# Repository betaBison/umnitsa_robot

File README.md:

# umnitsa_robot
Umnitsa comes from the englsih transliteration of the russian word "умница" clever pesron or smarty-pants.
Umnitsa is designed to be a clever robot.  
  
See also [umnitsa_msgs](https://github.com/betaBison/umnitsa_msgs), [umnitsa_gs](https://github.com/betaBison/umnitsa_gs), amd [umnitsa_mechanical](https://github.com/betaBison/umnitsa_mechanical).
  
umnitsa_robot is a [metapackage](http://wiki.ros.org/catkin/package.xml#Metapackages) for all the packages that run on the robot's computer. Packages are located in the `src/` directory and a brief description of each is included below.

## Setup
This package is currently compatible with the Raspberry Pi 3 B+ and Jetson Nano.
   
### Raspberry Pi
Install needed dependencies:  
`pip install`

### Jetson Nano
Install needed dependencies:  
`pip2 install Jetson.GPIO pygame nanpy`

Since this repo contains the realsesnse-ros repository as a submodule it's important to run the following command  
`git clone --recursive <URL to git repo>`  
If you failed to do this initially, then inside this repository run  
`git submodule update --init --recursive`  
The realsense-ros also requires the latest [Intel RealSense SDK](https://github.com/IntelRealSense/librealsense/releases). Jetson Nano [installation instructions](https://github.com/JetsonHacksNano/installLibrealsense).

#### Arduino Firmware
Follow directions here to upload correct firmware to arduino (https://github.com/nanpy/nanpy-firmware)

#### Pygame errors:
If there are erros installing pygame, you may need to add its dependencies.  
`sudo apt install libsdl1.2-dev python-dev libsdl-image1.2-dev libsdl-mixer1.2-dev libsdl-ttf2.0-dev libsdl1.2-dev libsmpeg-dev python-numpy subversion libportmidi-dev ffmpeg libswscale-dev libavformat-dev libavcodec-dev`

### Desktop
Since this repo contains the realsesnse-ros repository as a submodule it's important to run the following command  
`git clone --recursive <URL to git repo>`  
If you failed to do this initially, then inside this repository run  
`git submodule update --init --recursive`  
The realsense-ros also requires the latest [Intel RealSense SDK](https://github.com/IntelRealSense/librealsense/releases). Linux [installation instructions](https://github.com/IntelRealSense/librealsense/blob/master/doc/distribution_linux.md). You must install the dev package  
`sudo apt install librealsense2-dkms librealsense2-utils librealsense2-dev`   
   
Install pygame for the joystick controller  
`pip2 install pygame`

## Package Overview
### umnitsa_robot
Empty package that declares packages inside the [metapackage](http://wiki.ros.org/catkin/package.xml#Metapackages).

### umnitsa_robot_launch
This package contains parameters adn launch files for the umnitsa robot. Parameters should be adjusted for compatibility with system setup.

### umnitsa_hardware
This package consists of the harware interfacing nodes as follows:
#### motors
outputs to the motor control board to control four DC motors  

Normal mode:  
The max throttle going forward is 71% on all motors, not 100%. This is so that moving the joystick in a steady
circle produces a steady cirlce of robot movement.  

Turbo mode:  
If the joystick is moved at all, one of the motors is set to 100% throttle. This makes it faster, but unfit for precise movement.

#### RGB
Outputs to the UmnitsaRGB custom PCB  

#### ultrasonic
Inputs from the UmnitsaUltra custom PCB

### umnitsa_joystick
Package that contains the node that that receives input from a switch pro controller and outputs to the joystick message.

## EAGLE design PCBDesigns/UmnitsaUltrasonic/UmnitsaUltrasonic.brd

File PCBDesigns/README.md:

# Umnitsa Custom PCB Designs
Each folder contains the Eagle PCB schematic and board layout as well as the gerber files.

## UmnitsaControl
UmnitsaControl is the PCB for the motor control of four DC 12 V motors using two
Pololu-A4990 Motor Driver Carriers. Rated for 1.0 Amp for each motor and 2.5 Amp total.  
**Inputs:** 12 V supply, RasPi 10 control inputs  
**Outputs:** 12 V pins, 4 Motor Outputs, A4990 error pins (optional)  

## UmnitsaRGB
UmnitsaRGB is used to control 8 RGB LEDs with only 3 pin inputs from the RasPi by using
three HC595 shift registers.  
**Inputs:** 5 V supply, RasPi 3 control inputs  
**Outputs:** 5 V pins, 8 RGB LED Outputs  

## UmnitsaUltrasonic
UmnitsaRGB is used to receive data from four HC-SR04 ultrasonic sensors.  

**Inputs:** 5 V supply, RasPi control inputs  
**Outputs:** 5 V pins, 4 HC-SR04 inputs/outputs

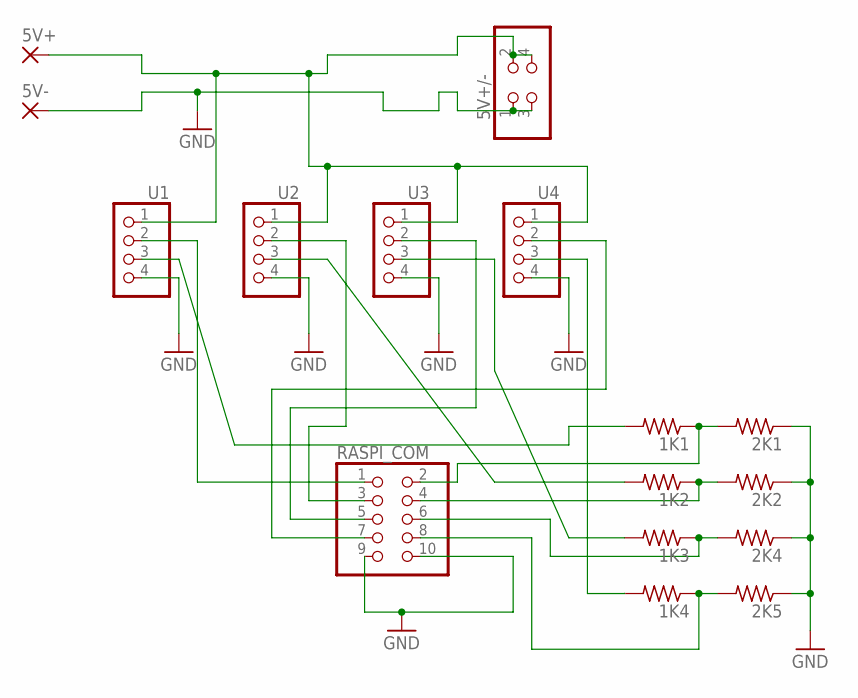
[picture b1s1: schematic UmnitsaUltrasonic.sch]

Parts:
1K1, 1K2, 1K3, 1K4, 2K1, 2K2, 2K4, 2K5: R-US_0204/7; 0204/7
5V+, 5V-: 3,17/1,3
5V+/-: PINHD-2X2; 2X02
RASPI_COM: PINHD-2X5; 2X05
U1, U2, U3, U4: PINHD-1X4; 1X04

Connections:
GND: 2K1.1, 2K2.1, 2K4.1, 2K5.1, 5V+/-.1, 5V+/-.3, 5V-.1, RASPI_COM.9, RASPI_COM.10, U1.4, U2.4, U3.4, U4.4
unnamed: 1K4.2, U4.3
unnamed: 1K3.2, U3.3
unnamed: 1K1.1, 2K1.2, RASPI_COM.2
unnamed: 1K2.1, 2K2.2, RASPI_COM.4
unnamed: 1K3.1, 2K4.2, RASPI_COM.6
unnamed: 5V+.1, 5V+/-.2, 5V+/-.4, U1.1, U2.1, U3.1, U4.1
unnamed: 1K4.1, 2K5.2, RASPI_COM.8
unnamed: RASPI_COM.1, U1.2
unnamed: RASPI_COM.3, U2.2
unnamed: RASPI_COM.5, U3.2
unnamed: RASPI_COM.7, U4.2
unnamed: 1K2.2, U2.3
unnamed: 1K1.2, U1.3

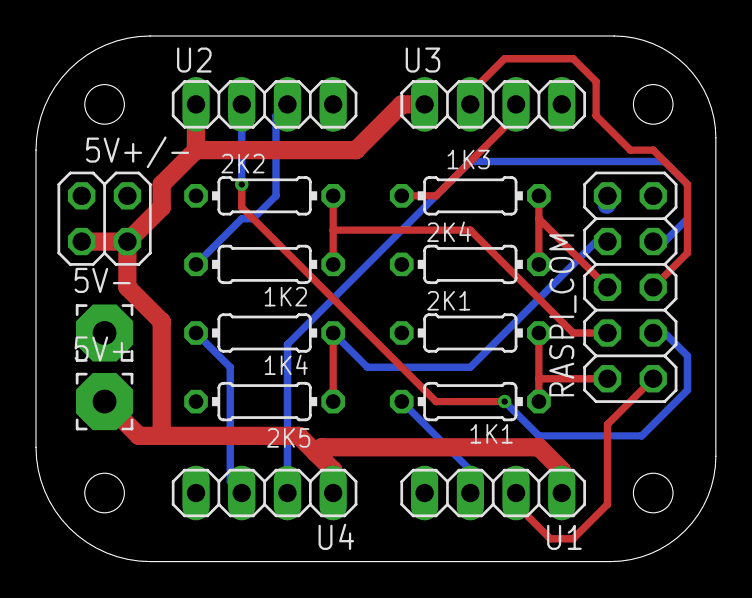
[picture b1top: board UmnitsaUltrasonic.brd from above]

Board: 2 copper layers, 37.8 x 29.2 mm, 16 parts (0 on the bottom side), 14 nets.

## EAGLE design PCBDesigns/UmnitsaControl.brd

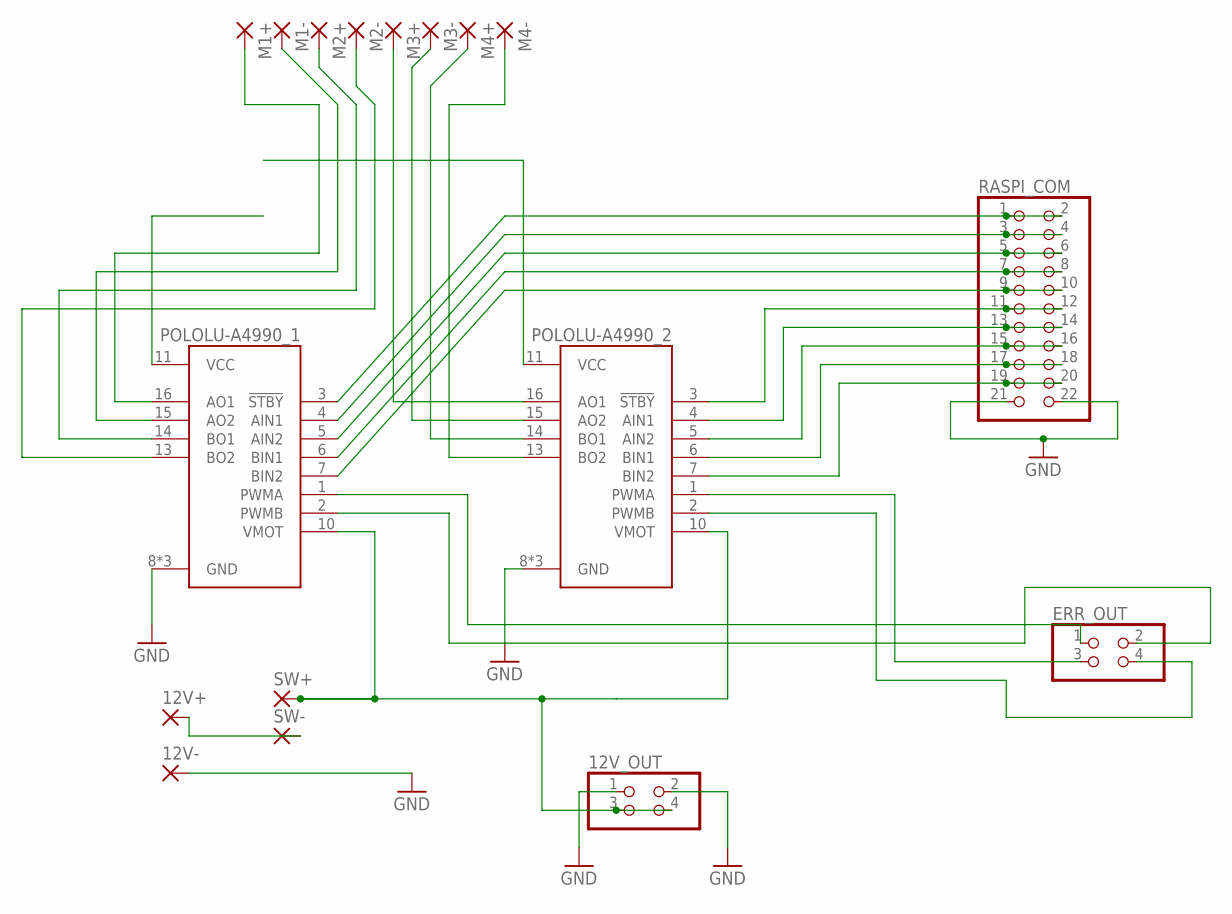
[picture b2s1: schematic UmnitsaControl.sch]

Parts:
12V+, 12V-: 3,81/1,4
12V_OUT: PINHD-2X2; 2X02
ERR_OUT: PINHD-2X2; 2X02
M1+, M1-, M2+, M2-, M3+, M3-, M4+, M4-: 3,81/1,4
POLOLU-A4990_1, POLOLU-A4990_2: POLOLU-713; SHIELD_POLOLU-713
RASPI_COM: PINHD-2X11; 2X11
SW+: 2,54/1,0
SW-: 2,54/1,0

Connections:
GND: 12V-.1, 12V_OUT.1, 12V_OUT.2, POLOLU-A4990_1.8 (GND), POLOLU-A4990_1.9 (GND), POLOLU-A4990_1.12 (GND), POLOLU-A4990_2.8 (GND), POLOLU-A4990_2.9 (GND), POLOLU-A4990_2.12 (GND), RASPI_COM.21, RASPI_COM.22
unnamed: M1+.1, POLOLU-A4990_1.16 (AO1)
unnamed: M1-.1, POLOLU-A4990_1.15 (AO2)
unnamed: 12V+.1, SW-.1
unnamed: M2+.1, POLOLU-A4990_1.14 (BO1)
unnamed: M2-.1, POLOLU-A4990_1.13 (BO2)
unnamed: M3+.1, POLOLU-A4990_2.16 (AO1)
unnamed: M3-.1, POLOLU-A4990_2.15 (AO2)
unnamed: M4+.1, POLOLU-A4990_2.14 (BO1)
unnamed: M4-.1, POLOLU-A4990_2.13 (BO2)
unnamed: POLOLU-A4990_2.3 (!STBY), RASPI_COM.11, RASPI_COM.12
unnamed: POLOLU-A4990_2.7 (BIN2), RASPI_COM.19, RASPI_COM.20
unnamed: POLOLU-A4990_2.6 (BIN1), RASPI_COM.17, RASPI_COM.18
unnamed: POLOLU-A4990_2.5 (AIN2), RASPI_COM.15, RASPI_COM.16
unnamed: POLOLU-A4990_2.4 (AIN1), RASPI_COM.13, RASPI_COM.14
unnamed: POLOLU-A4990_1.3 (!STBY), RASPI_COM.1, RASPI_COM.2
unnamed: POLOLU-A4990_1.4 (AIN1), RASPI_COM.3, RASPI_COM.4
unnamed: POLOLU-A4990_1.5 (AIN2), RASPI_COM.5, RASPI_COM.6
unnamed: POLOLU-A4990_1.6 (BIN1), RASPI_COM.7, RASPI_COM.8
unnamed: POLOLU-A4990_1.7 (BIN2), RASPI_COM.9, RASPI_COM.10
unnamed: ERR_OUT.3, POLOLU-A4990_2.1 (PWMA)
unnamed: ERR_OUT.4, POLOLU-A4990_2.2 (PWMB)
unnamed: ERR_OUT.1, POLOLU-A4990_1.1 (PWMA)
unnamed: ERR_OUT.2, POLOLU-A4990_1.2 (PWMB)
unnamed: 12V_OUT.3, 12V_OUT.4, POLOLU-A4990_1.10 (VMOT), POLOLU-A4990_2.10 (VMOT), SW+.1

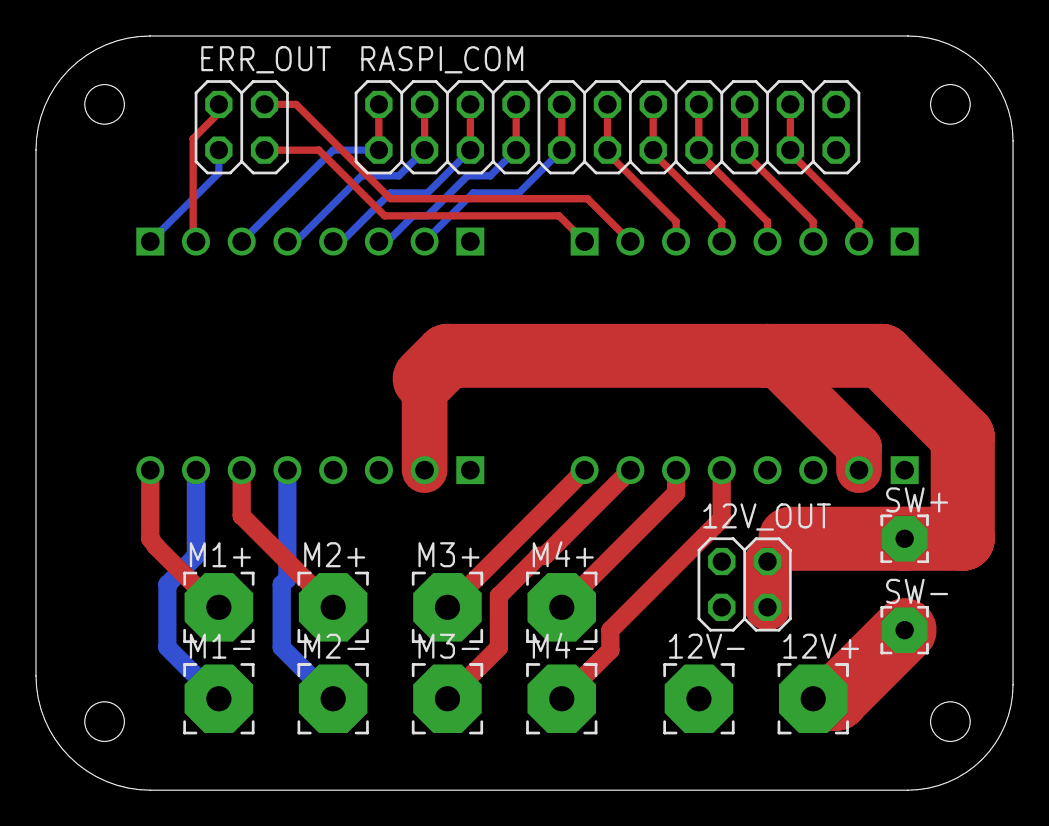
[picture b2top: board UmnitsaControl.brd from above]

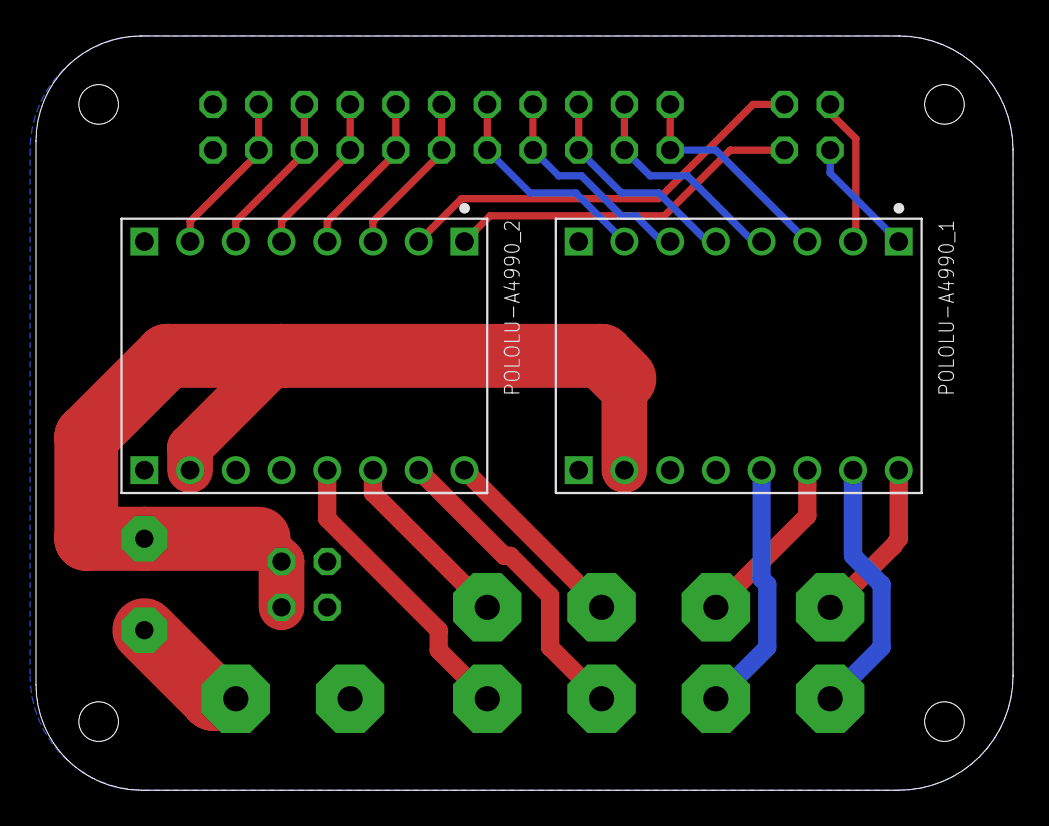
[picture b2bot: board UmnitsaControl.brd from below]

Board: 2 copper layers, 54.3 x 41.9 mm, 17 parts (2 on the bottom side), 25 nets.

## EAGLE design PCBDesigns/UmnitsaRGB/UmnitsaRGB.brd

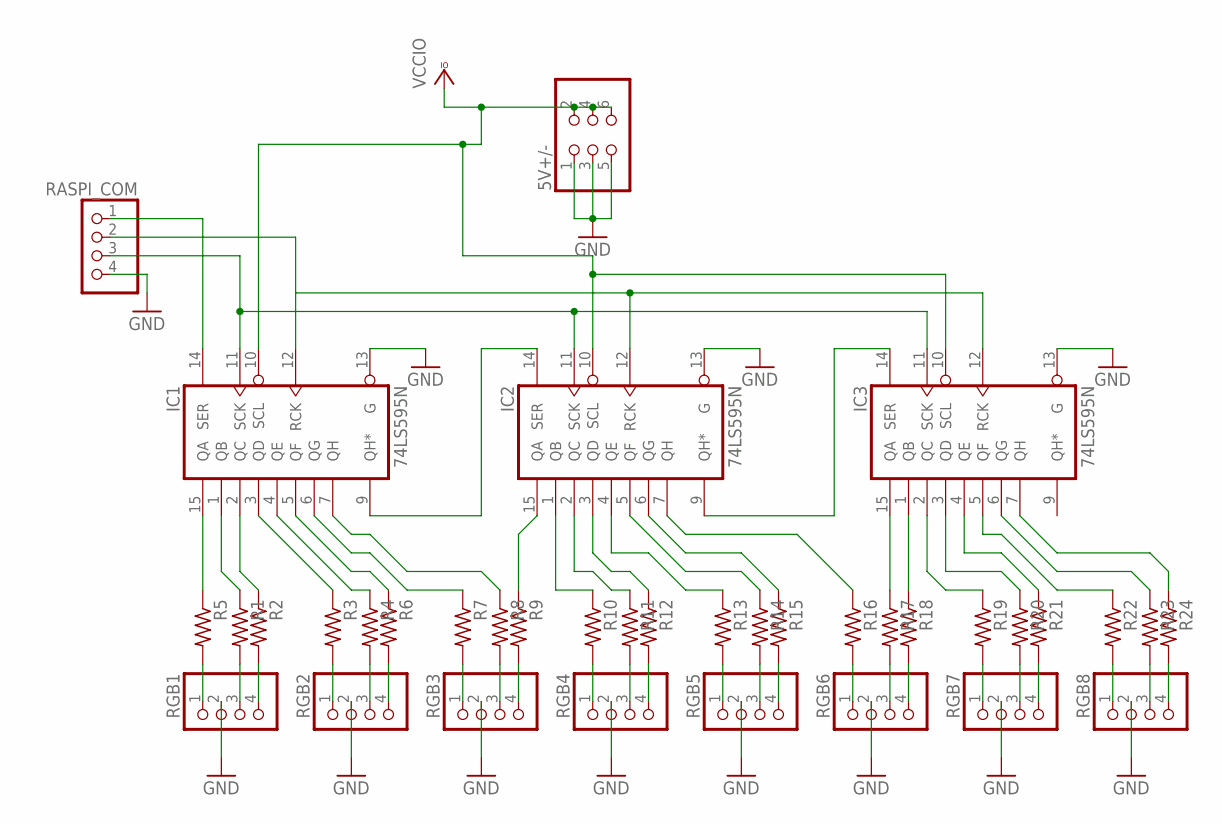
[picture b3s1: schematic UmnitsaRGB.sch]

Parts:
5V+/-: PINHD-2X3; 2X03
IC1, IC2, IC3: 74LS595N; DIL16
R1, R2, R3, R4, R5, R6, R7, R8, R9, R10, R11, R12, R13, R14, R15, R16, R17, R18, R19, R20, R21, R22, R23, R24: R-US_0204/7; 0204/7
RASPI_COM: PINHD-1X4; 1X04
RGB1, RGB2, RGB3, RGB4, RGB5, RGB6, RGB7, RGB8: PINHD-1X4; 1X04

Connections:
GND: 5V+/-.1, 5V+/-.3, 5V+/-.5, IC1.8 (GND), IC1.13 (G), IC2.8 (GND), IC2.13 (G), IC3.8 (GND), IC3.13 (G), RASPI_COM.4, RGB1.2, RGB2.2, RGB3.2, RGB4.2, RGB5.2, RGB6.2, RGB7.2, RGB8.2
unnamed: R5.2, RGB1.1
unnamed: R1.2, RGB1.3
unnamed: R2.2, RGB1.4
unnamed: R3.2, RGB2.1
unnamed: R4.2, RGB2.3
unnamed: R6.2, RGB2.4
unnamed: R7.2, RGB3.1
unnamed: R8.2, RGB3.3
unnamed: R9.2, RGB3.4
unnamed: R10.2, RGB4.1
unnamed: R11.2, RGB4.3
unnamed: R12.2, RGB4.4
unnamed: R13.2, RGB5.1
unnamed: R14.2, RGB5.3
unnamed: R15.2, RGB5.4
unnamed: R16.2, RGB6.1
unnamed: R17.2, RGB6.3
unnamed: R18.2, RGB6.4
unnamed: IC1.14 (SER), RASPI_COM.1
unnamed: IC1.12 (RCK), IC2.12 (RCK), IC3.12 (RCK), RASPI_COM.2
unnamed: IC1.9 (QH*), IC2.14 (SER)
unnamed: IC2.9 (QH*), IC3.14 (SER)
unnamed: IC1.11 (SCK), IC2.11 (SCK), IC3.11 (SCK), RASPI_COM.3
unnamed: IC1.15 (QA), R5.1
unnamed: IC1.1 (QB), R1.1
unnamed: IC1.2 (QC), R2.1
unnamed: IC1.3 (QD), R3.1
unnamed: IC1.4 (QE), R4.1
unnamed: IC1.5 (QF), R6.1
unnamed: IC1.6 (QG), R7.1
unnamed: IC2.1 (QB), R10.1
unnamed: IC2.15 (QA), R9.1
unnamed: IC1.7 (QH), R8.1
unnamed: IC2.2 (QC), R11.1
unnamed: IC2.3 (QD), R12.1
unnamed: IC2.4 (QE), R13.1
unnamed: IC2.5 (QF), R14.1
unnamed: IC2.6 (QG), R15.1
unnamed: IC2.7 (QH), R16.1
unnamed: IC3.15 (QA), R17.1
unnamed: IC3.1 (QB), R18.1
unnamed: IC3.2 (QC), R19.1
unnamed: IC3.3 (QD), R20.1
unnamed: IC3.4 (QE), R21.1
unnamed: IC3.5 (QF), R22.1
unnamed: IC3.6 (QG), R23.1
unnamed: IC3.7 (QH), R24.1
unnamed: R19.2, RGB7.1
unnamed: R20.2, RGB7.3
unnamed: R21.2, RGB7.4
unnamed: R22.2, RGB8.1
unnamed: R23.2, RGB8.3
unnamed: R24.2, RGB8.4
VCC: IC1.16 (VCC), IC2.16 (VCC), IC3.16 (VCC)
VCCIO: 5V+/-.2, 5V+/-.4, 5V+/-.6, IC1.10 (SCL), IC2.10 (SCL), IC3.10 (SCL)

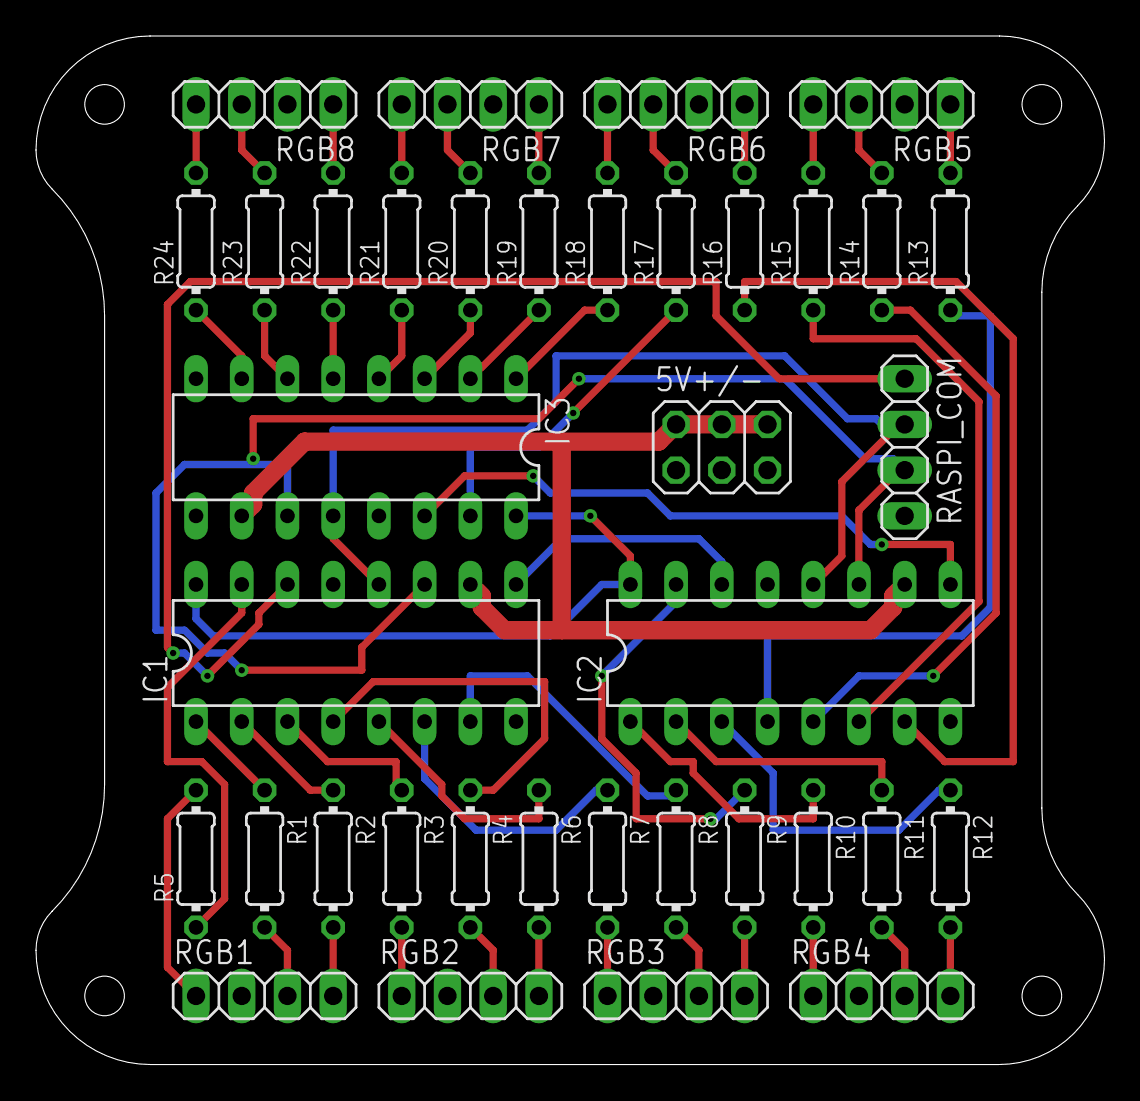
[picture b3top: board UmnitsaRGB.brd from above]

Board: 2 copper layers, 59.4 x 57.1 mm, 37 parts (0 on the bottom side), 56 nets.

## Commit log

2016-02-11 shorter timeout
2016-02-11 each RGB slowly
2016-02-11 tab error, working now on rpi
2016-02-11 testing on rpi
2016-02-11 24 leds for template
2019-03-12 single motor testing
2019-03-12 basic pwm movement test
2019-03-13 motor pins global
2019-03-13 not all global tho
2019-03-13 notifiers
2019-03-13 delay
2019-03-18 software pwm and ultrasonic test
2019-03-18 syntax errors
2019-03-18 add a colon and name
2019-03-18 timing change
2019-03-18 better timing
2019-03-18 change print statement
2019-03-18 full thing
2019-03-18 forever test
2019-03-18 ros framework
2019-03-21 rgb test
2019-03-21 spacing diff
2019-03-21 spaces to tabs
2019-03-21 print error
2019-03-21 self typos
2019-03-21 some blinking
2019-03-23 PCB Design files
2019-03-23 PCB documentation
2019-03-23 file name error
2019-03-23 file name change
2019-03-23 current rating for UmnitsaControl
2019-03-23 auto bluetooth connect
2019-03-24 switch pro controller test
2019-03-24 off upon ending
2019-03-24 joystick and rgb ros nodes
2019-03-24 remove ros files
2019-03-24 added ros files to .gitignore
2019-03-24 rgb node working on hardware
2019-03-24 remove CMakeLists.txt
2019-03-24 remove cmake
2019-03-24 4 button test
2019-03-24 trying bits
2019-03-24 bit shifting
2019-03-24 reverse order bit control
2019-03-24 2 Hz joystick
2019-03-24 only publish axis at 2Hz
2019-03-24 speed up publisher/subscriber
2019-03-27 remove CMakeLists
2019-03-27 moved lister/subscriber example to testing
2019-03-27 added all joystick buttons
2019-03-28 update joystick message
2019-03-29 testing on hardware
2019-03-29 ignore CMake!
2019-03-29 removed CMakeLists.txt
2019-03-29 rgb template
2019-03-29 created readme outline
2019-03-29 button priority msg, global pin names
2019-03-30 global pins
2019-03-30 pin change
2019-03-30 rgb testing
2019-03-30 GPIO.cleanup
2019-03-30 ultrasonic publisher
2019-03-30 start of motor subscriber
2019-03-30 executable
2019-03-30 convert to tabs
2019-03-30 added ultrasonic message
2019-03-30 bugs in ultra
2019-03-30 cw testing
2019-03-30 owm clockwise
2019-03-30 lateral motion
2019-03-30 lateral movement SUCCESS!
2019-03-31 correct lateral direction
2019-03-31 joystick calibration
2019-03-31 lateral + rotation
2019-03-31 lateral + rotation success
2019-04-06 prevent over waiting with default value
2019-04-06 max wait time for ulta node
2019-04-06 temp distance list
2019-04-06 error handling
2019-04-06 measure function
2019-04-06 echoes are GPIO.IN, duh
2019-04-09 poweroff
2019-04-09 turbo mode
2019-04-18 pin changes
2019-04-18 turn off turbo
2019-04-18 error check on joystick init
2019-04-18 send error array
2019-04-18 only sent axis at 10Hz
2019-04-18 change axis back to 0.0
2019-04-18 update timer
2019-04-18 don't constantly publish 0
2019-04-19 joystick and motor launch
2019-04-19 test each rgb
2019-04-19 renamed launch
2019-04-19 scaling lateral
2019-04-19 global clearance
2019-04-19 cleanup
2019-04-19 discretize LEDs
2019-04-19 start rgb and ultrasonic
2019-04-19 correct magnitude right toggle
2019-04-19 ros raspberry readme
2019-04-19 standard publisher name
2019-04-25 moved messages into separate package
2019-05-08 build/ and devel/ no longer relevant
2019-05-08 anonymity not needed
2019-05-09 move subdirectories into new repositories
2019-05-09 basic tf publish/subscriber
2019-05-09 changed umnitsa_rpi to a metapackage
2019-05-10 update package name
2019-05-10 metapackage package
2019-05-14 breakdown into pkgs
2019-05-14 launch edit
2019-05-14 pull from ros parameter server
2019-05-14 update readme to reflect new pkg organization
2019-05-17 capitalize msg types
2019-05-17 simple proportional control example
2019-05-20 rplidar source software
2019-05-20 cleanup rplidar package
2019-05-21 working on pi
2019-05-21 added realsense-ros
2019-05-22 conforming motors
2019-05-22 joy cmd_vel
2019-05-22 config for rpi
2019-05-23 cross compatibility: architecture check
2019-05-24 added other repo references
2019-05-28 webcam publisher
2019-06-04 realsense-ros setup instructions
2019-06-20 added desktop install instructions
2019-08-13 add license
2020-02-09 nano arduino implementation
2020-02-09 typos
2020-02-11 startup service files
2020-02-11 added roscore service
